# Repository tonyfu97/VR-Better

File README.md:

# VR-Better
Uses haptic feedback to address Visually Induced Motion Sickness (VIRS) in VR. 

by Tony Fu, Sivathanu Kumar, Hon Keat Chan

## Introduction

In this project, we propose a solution to counteract the nausea often experienced by Virtual Reality (VR) users, a consequence of a lack of intuitive awareness within their virtual environments. Our approach employs tactile stimuli, conveyed through subtle vibrations from small motors mounted behind the user's ears. These signals guide user attention towards specific areas within the VR environment, which in turn reduces the need for VR content creators to rotate their scenes—a common cause of user discomfort and sickness.

Our system is not exclusive to VR environments; it also offers benefits in real-world settings. Owing to the immersive nature of VR, users can frequently lose awareness of their actual surroundings, potentially putting themselves at risk. Our solution addresses this issue by using lighted indicators that simultaneously signal to bystanders about the user's presence or intended direction. Additionally, the device is equipped with sensors that capture and log data from the built-in accelerometer and gyroscope, providing users with the opportunity to adjust the intensity of the vibration motors. This approach enhances both user safety and the overall VR experience.

## Design

The project undergoes three design iterations. Our initial prototype was developed on a breadboard, employing an Arduino Nano 33 BLE for control of four small vibration motors through BJT circuits (**Figure 1**). Two of these motors were designed with malleable steel wires for convenient ear mounting. This first prototype successfully established communication with a Quest 2 headset using the [Arduino Bluetooth Plugin](https://assetstore.unity.com/packages/tools/input-management/arduino-bluetooth-plugin-98960#description) from Unity Asset Store (**Figure 2**).

**Figure 1**: Initial Prototype. This image depicts our initial prototype, constructed using a breadboard. It incorporates an Arduino Nano 33 BLE, which independently controls each small motor through a BJT circuit. The four vibration motors, denoted by the cyan box, include two that come equipped with malleable steel wires for mounting behind the user's ears. This prototype successfully establishes communication with the Quest 2 headset, enabling transmission of motor commands.

**Figure 2**: Block Diagram of Initial Prototype. This diagram provides an overview of the initial prototype's architecture. The Oculus Headset houses an application developed using Unity, utilizing the XR Interaction Toolkit to facilitate integration with the VR headset (for instance, obtaining the position of the headset). Virtual objects of interest are tagged; when these objects come within five units of virtual distance from the user's virtual camera, they activate the proximity detection component. This element calculates the suitable intensity for the four motors (up, down, left, right) based on the relative position of the object to the user. Subsequently, the Arduino Bluetooth Plugin communicates with the Motor Driver Circuit, which actuates the vibration motors as needed.

For the second prototype, we transitioned to a custom PCB design, powered by a single coin cell battery (**Figure 3**). We incorporated capacitors to stabilize the current; however, the coin cell battery was insufficient in supplying the necessary current for the motors.

**Figure 3**: Second Prototype. Our customized second prototype is designed with a PCB and powered by a single coin cell battery. In an attempt to stabilize the current, we incorporated some capacitors into the design. However, we encountered an issue where the coin cell battery was insufficient in providing the necessary current to operate the motors.

Based on our experience with the first two prototypes, our third iteration combined ultrasound rangefinders with vibration motors and LED lights. The updated design aimed to alert users about both the virtual and real objects around them and signal their probable direction of movement to observers. **Figure 4** shows the physical architecture of the VRbetter augmentation device. The same design is intended to:

1. In VR environments, provide a Bluetooth channel from the CPU driving the virtual environment to a pair of vibration motors mounted behind the ears of the VR user to alert the user to ‘happenings’ behind the user within the virtual environment. This negates the need for the user inhabiting the virtual environment having the need to keep looking as the user currently gets little to no hints as one would in the real world.
2. In the real world, senses for approaching objects from behind the user, simultaneously provide lighted indicators to signal to the approaching party of the presence or intended direction of the user, and provide the user enhanced awareness of the distance and or approaching speed towards the user from the back via a pair of vibration motors mounted to the back of the user’s ears. It may be used as a personal safety for joggers or bicyclists.  
3. Capture and log accelerometer and gyroscope data from the built in IMU to allow the user to acknowledge or ‘tone-down’ the intensity of the vibration motors.
4. With additional sensors to the front, provide a visually impaired user a means to detect obstacles.

The device is currently powered from a ubiquitous USB power pack probably most conveniently mounted in a pocket at the lower back of the user as is commonly found in bicyclist or jogger apparel.

**Figure 4**: VRbetter Hardware Schematic. This diagram details the configuration of the VRbetter device. At the heart of the system, the Arduino Nano 33 BLE processes inputs from two ultrasound rangefinders. It then outputs instructions to two vibration motors and 12 red LEDs (6 per side) via the 16-channel PCA 9685 PWM controller.

**Figure 5**: VRbetter hardware mounted on the back of the Oculus Quest Pro virtual reality headset. Vibration motors are tucked into the fabric headband behind the ears of the mannequin.

**Figure 6**: Side view of **Figure 5**.

**Figure 7**: View again from the back. Note the LEDs and PWM driver are mounted on a velcro strip to be mounted to the back of the shoulders of the user.

## Early Results

Our initial experiments involved attaching vibration motors insecurely to the back of the ears and the forehead. These setups demonstrated that even when a motor was weakly activated without the wearer's awareness, it could prompt a response to move the head in the direction of the vibration. For instance, as depicted in **Figure 8**, the activation of the left motor (represented in green) occasionally incited a leftward turn from the user (blue line).

However, these responses did not demonstrate a linear correlation, with the user's response and the motor's intensity showing no clear relationship. In particular, the right motor's attachment was insufficient, leading to the user having difficulty sensing its vibration (red line in **Figure 8**).

**Figure 8**: Example trial of user response to tactile stimulation. The plot displays the y-axis gyroscope readings (in arbitrary units) alongside the corresponding left and right motor intensities. The angular velocity (blue line) represents the readings from the gyroscope. The green and red lines indicate the intensities of the left and right motors, respectively. 

Another challenge we encountered was the inconsistent quality of electrical connections to the motors, likely due to the breadboard nature of our wiring. To address these issues, we aimed to develop more secure setups. However, our efforts were cut short by time constraints before we could conduct more advanced experimentation.

We developed a simple VR game as a testing ground for the communication between the motor driving circuit and the Oculus headset. The game is designed with a single moving object that rotates counterclockwise around the player (**Figure 9**). The game actuates the motors depending on the sphere's relative position to the player's head. Anecdotal evidence from the test subject suggested he could discern the ball's left or right position based on the tactile cues received from the VR device.

**Figure 9**: Top-Down View of a Simple VR Testing Game. In the center is the user standing on a green platform. A yellow ball rotates counterclockwise around the user, serving as the stimulus for activating the left and right vibration motors. These motors communicate the position of the moving sphere relative to the user, enhancing spatial awareness within the VR environment.

## Continuing Work
* Our current model utilizes the HC-SR04 ultrasonic sensor with a limited range of 13ft. However, we are exploring the integration of a Time-of-Flight (ToF) sensor, specifically the VL53L4CX. By mounting this on a custom PCB with an identical pinout, we could potentially detect objects up to 3m away.
* We are also working on a custom printed circuit board for the CPU and IMU. This improved model would feature expanded non-volatile memory for more robust data logging capabilities.
* To aid visually impaired users, we aim to add ranging and other types of sensors to the front of the device.
* Continuous development is underway to enhance the software that interfaces with VR games and environment.

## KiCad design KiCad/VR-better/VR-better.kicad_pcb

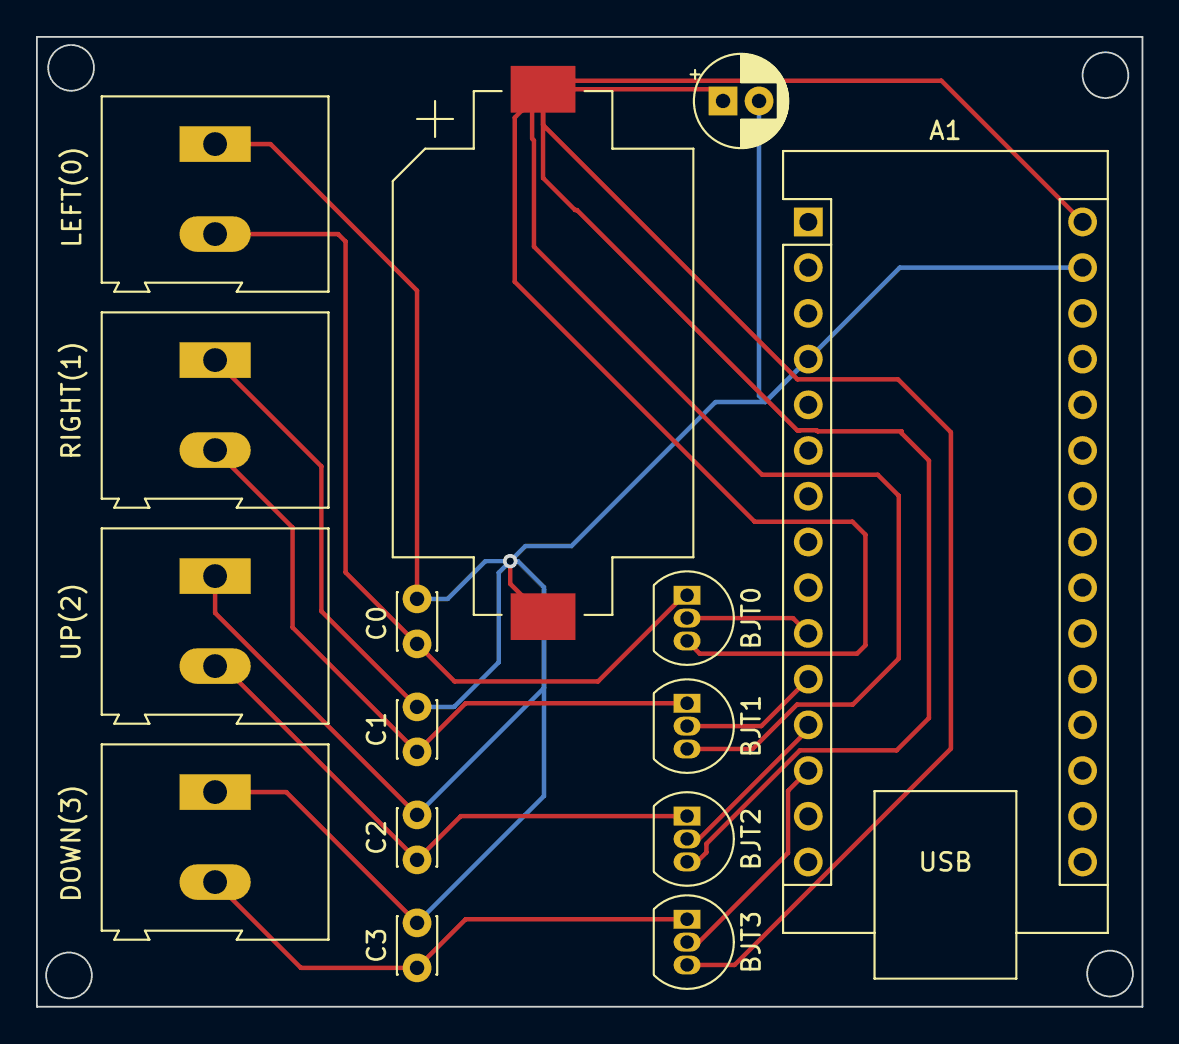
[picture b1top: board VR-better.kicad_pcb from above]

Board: 2 copper layers, 61.4 x 53.9 mm, 15 parts (0 on the bottom side), 10 nets.

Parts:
A1: Arduino_Nano_v3.x; Arduino_Nano
BJT0, BJT1, BJT2, BJT3: 2N3904; TO-92_Inline
BT1: Battery_Cell; BatteryHolder_Keystone_1060_1x2032
C0, C1, C2, C3: 0.1 uF; C_Disc_D3.0mm_W2.0mm_P2.50mm
C_Pow1: 100 uF; CP_Radial_D5.0mm_P2.00mm
DOWN(3): Screw_Terminal_01x02; TerminalBlock_Altech_AK300-2_P5.00mm
LEFT(0): Screw_Terminal_01x02; TerminalBlock_Altech_AK300-2_P5.00mm
RIGHT(1): Screw_Terminal_01x02; TerminalBlock_Altech_AK300-2_P5.00mm
UP(2): Screw_Terminal_01x02; TerminalBlock_Altech_AK300-2_P5.00mm

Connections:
GND: A1.4 (GND), A1.29 (GND), BT1.2 (-), C0.2, C1.2, C2.2, C3.2, C_Pow1.2, DOWN(3).1, LEFT(0).1, RIGHT(1).1, UP(2).1
unnamed: A1.10 (D7), BJT0.2 (B)
unnamed: A1.11 (D8), BJT1.2 (B)
unnamed: A1.12 (D9), BJT2.2 (B)
unnamed: A1.13 (D10), BJT3.2 (B)
unnamed: A1.30 (VIN), BJT0.3 (C), BJT1.3 (C), BJT2.3 (C), BJT3.3 (C), BT1.1 (+), C_Pow1.1
unnamed: BJT0.1 (E), C0.1, LEFT(0).2
unnamed: BJT1.1 (E), C1.1, RIGHT(1).2
unnamed: BJT2.1 (E), C2.1, UP(2).2
unnamed: BJT3.1 (E), C3.1, DOWN(3).2

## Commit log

2023-05-12 remove unused files
2023-06-08 include report pdf
2023-06-16 Add figures
